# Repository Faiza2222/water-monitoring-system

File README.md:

# water-monitoring-system

# Collaborators
1. Masika Stephanie - Supervisor
2.

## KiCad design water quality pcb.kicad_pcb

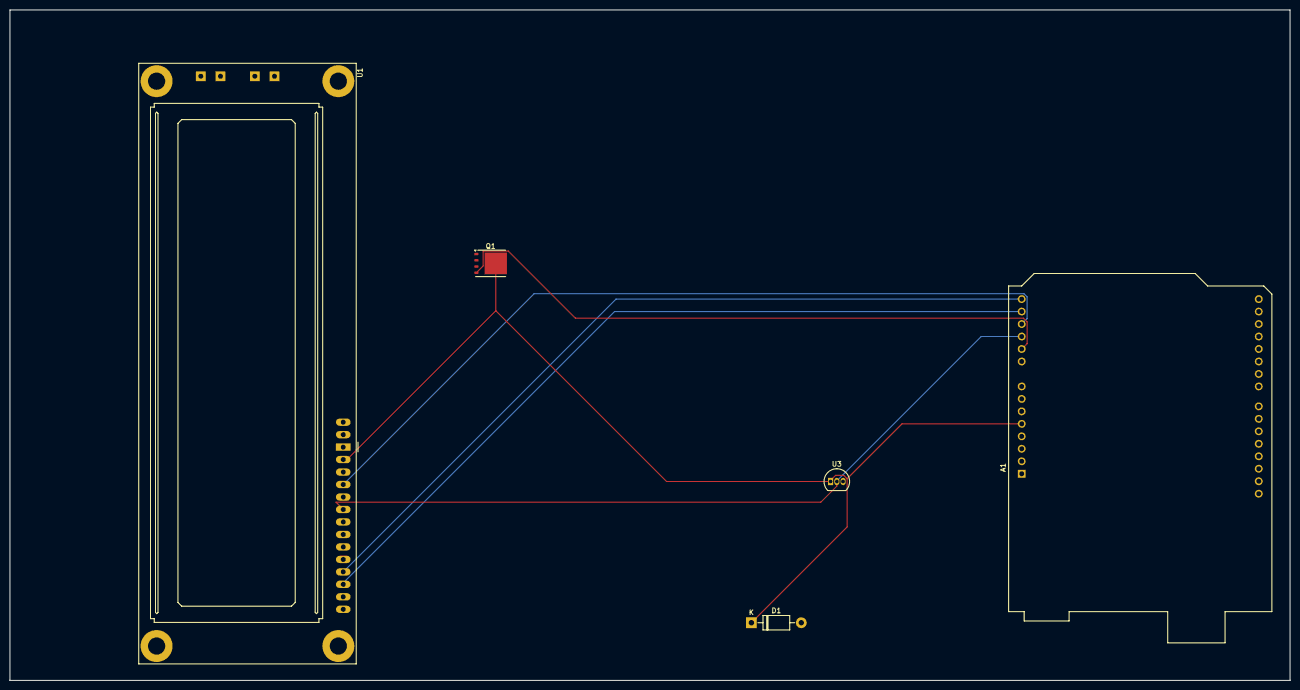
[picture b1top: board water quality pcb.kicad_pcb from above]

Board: 2 copper layers, 260.6 x 136.5 mm, 5 parts (0 on the bottom side), 6 nets.

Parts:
A1: Arduino_UNO_R2
D1: 1N4007; D_DO-41_SOD81_P10.16mm_Horizontal
Q1: BSC13DN30NSFD; TDSON-8-1
U1: LCD-016N002L
U3: LM35-LP; TO-92_Inline

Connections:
+5V: A1.5 (+5V), D1.1 (K), Q1.5 (D), U1.2 (VDD), U3.1 (+V_{S})
unnamed: A1.10 (A1), Q1.4 (G)
unnamed: A1.11 (A2), U1.6 (E), U3.2 (V_{OUT})
unnamed: A1.12 (A3), U1.4 (RS)
unnamed: A1.14 (SCL/A5), U1.11 (DB4)
unnamed: A1.13 (SDA/A4), U1.12 (DB5)
